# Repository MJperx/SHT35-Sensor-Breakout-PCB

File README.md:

# SHT35-Sensor-Breakout-PCB
PCB files for the Sensirion SHT35 Sensor Breakout

Format is KiCAD schematic and board layout

Designed by Jozsef Madar.  
Creative Commons Attribution, Share-Alike license
All text above must be included in any redistribution

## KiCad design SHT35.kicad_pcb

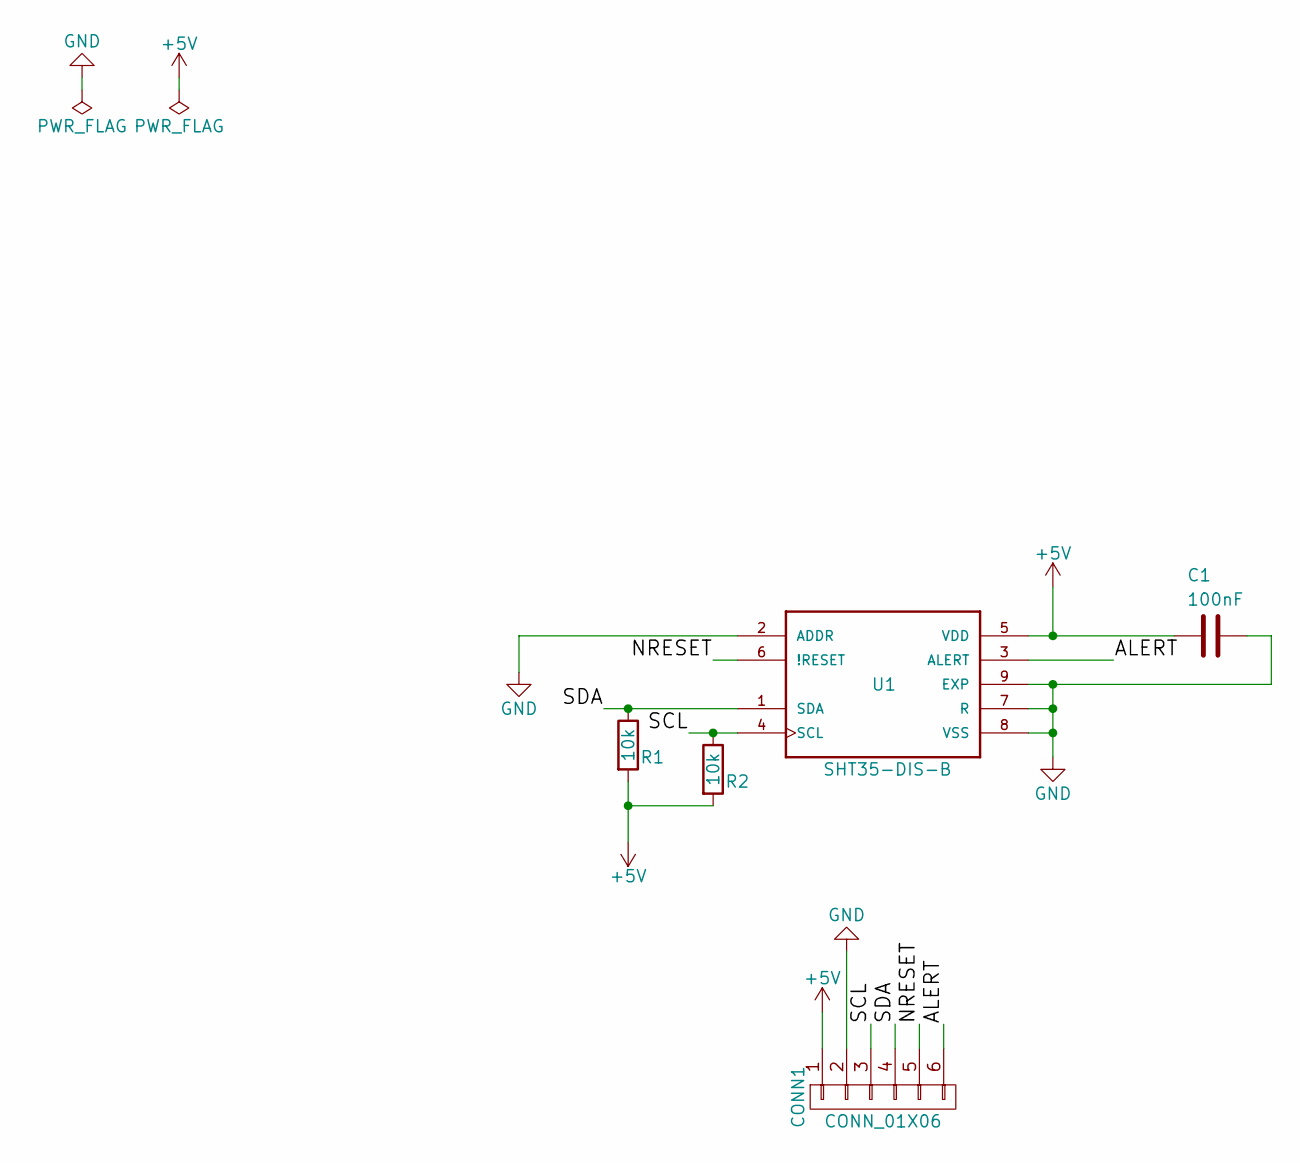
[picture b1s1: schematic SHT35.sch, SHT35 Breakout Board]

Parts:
C1: 100nF; C_0603_HandSoldering
CONN1: CONN_01X06; Pin_Header_Straight_1x06_Pitch2.54mm
R1, R2: 10k; R_0805_HandSoldering
U1: SHT35-DIS-B; dfn8

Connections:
+5V: C1.2, CONN1.1, R1.2, R2.2, U1.5 (VDD)
/ALERT: CONN1.6, U1.3 (ALERT)
/NRESET: CONN1.5, U1.6 (!RESET)
/SCL: CONN1.3, R2.1, U1.4 (SCL)
/SDA: CONN1.4, R1.1, U1.1 (SDA)
GND: C1.1, CONN1.2, U1.2 (ADDR), U1.7 (R), U1.8 (VSS), U1.9 (EXP)

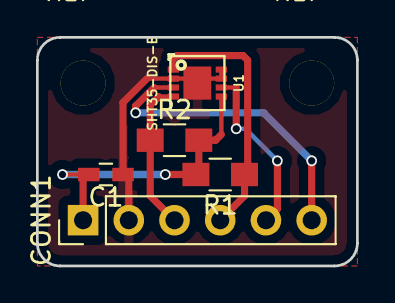
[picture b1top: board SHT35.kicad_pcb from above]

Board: 2 copper layers, 17.8 x 12.7 mm, 5 parts (0 on the bottom side), 6 nets.

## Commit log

2017-04-04 Add files
